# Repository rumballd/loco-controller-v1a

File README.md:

# loco-controller-v1a

NEW - Jan 2026, additional firmware examples and Handheld controller firmware

The Loco Controller is designed to offer a simple upgrade of Dapol and other locomotives to battery power and wireless control. It is highly integrated, incorporating an ESP32-C6 dual core MCU (microcontroller Unit) module together with a motor driver, voltage booster, battery charger and input power conditioner all on a single double sided PCB. 

The controller is designed as an exact replacement for the factory fitted DCC decoder adaptor installed in newer Dapol locomotives and installation consists of sliding out the factory PCB and replacing it with the controller. On the 58XX and B4 models the battery also slides in underneath the controller and is connected directly to the controller PCB.

For non Dapol locomotives there are a range of signals and power sources available on 2.54mm spacing pin headers including motor drive and LED outputs. In these cases though some disassembly of the locomotive body and soldering will be required.

Although designed primarily as a controller for motorised devices the device can also function as a generic wireless interface for signals, turnouts and other accessories. In such a ‘fixed’ application the unit can operate without a connected battery being powered solely by externally connected power sources and can drive multiple LED or servo outputs.

The controller implements a Wi-Fi access point and Web server that serves a page of locomotive specific controls to any standard web browser on a phone or tablet 

The initial hardware and firmware release supports:-

• Connector compatible with Dapol 0 Gauge 58XX and B4 locomotives

• Aux connector for other models with power, motor, LED and servo drive

• Integral voltage boost from VBAT to 12 V for the motor at 1 A

• Integral battery charger with power in via track or USB and 2mm JST socket for a 1S Li-Po battery

• Track power input is compatible with DCC and can be up to +-50 VDC with protection against inductive
 spikes
• Battery voltage and USB voltage can be monitored in firmware

• Links provided to isolate track power and the battery

• Charging is indicated by firebox LEDs in Dapol models and also in UI

• Multiple levels of over-current/over-voltage/over-temperature protection

• Integral Wi-Fi access point and Web server

• Control by standard Web browsers (up to four simultaneous connections)

• Firmware is updatable via USB connection

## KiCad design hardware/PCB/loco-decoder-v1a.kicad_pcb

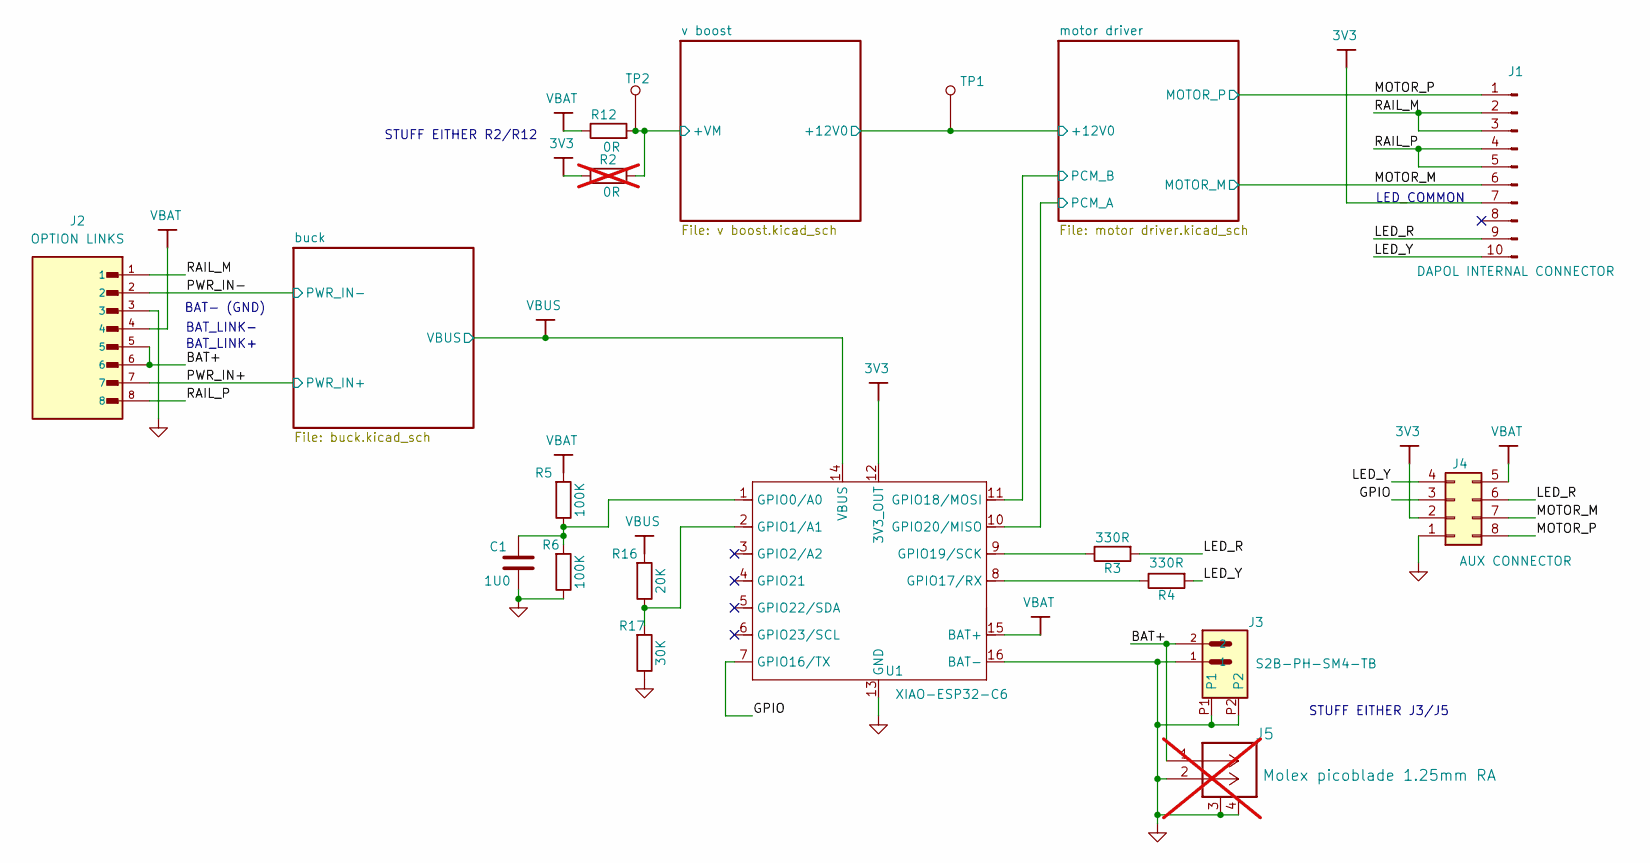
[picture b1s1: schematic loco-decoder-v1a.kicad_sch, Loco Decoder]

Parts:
C1: 1U0; C_0805_2012Metric
J1: DAPOL INTERNAL CONNECTOR; EDAC 302 SERIES CARD EDGE CONNECTOR 10way 2 row
J2: OPTION LINKS; HARWIN_M20-8890845
J3: S2B-PH-SM4-TB; JST_S2B-PH-SM4-TB
J4: AUX CONNECTOR; PinHeader_2x04_P2.54mm_Vertical
J5: Molex picoblade 1.25mm RA; CONN_532610001-SD_02_MOL; not fitted
R2: 0R; R_0805_2012Metric; not fitted
R3, R4: 330R; R_0805_2012Metric
R5, R6: 100K; R_0805_2012Metric
R12: 0R; R_0805_2012Metric
R16: 20K; R_0805_2012Metric
R17: 30K; R_0805_2012Metric
TP1, TP2: 3_Through hole test point; Test Point 1mm
U1: XIAO-ESP32-C6; XIAO-ESP32C6-SMD

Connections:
3V3: J1.7, J4.2, R2.1, U1.12 (3V3_OUT)
/BAT+: J2.5, J2.6, J3.2, J5.1
/GPIO: J4.3, U1.7 (GPIO16/TX)
/LED_R: J1.9, J4.6, R3.2
/LED_Y: J1.10, J4.4, R4.2
/MOTOR_M: J1.6, J4.7; also elsewhere on the board
/MOTOR_P: J1.1, J4.8; also elsewhere on the board
/PWR_IN+: J2.7; also elsewhere on the board
/PWR_IN-: J2.2; also elsewhere on the board
/RAIL_M: J1.2, J1.3, J2.1
/RAIL_P: J1.4, J1.5, J2.8
/motor driver/+12V0: TP1.1; also elsewhere on the board
/motor driver/PCM_A: U1.10 (GPIO20/MISO); also elsewhere on the board
/motor driver/PCM_B: U1.11 (GPIO18/MOSI); also elsewhere on the board
/v boost/+VM: R2.2, R12.2, TP2.1; also elsewhere on the board
GND: C1.2, J2.3, J3.1, J3.P1, J3.P2, J4.1, J5.2, J5.3, J5.4, R6.1, R17.1, U1.13 (GND), U1.16 (BAT-); also elsewhere on the board
unnamed: C1.1, R5.1, R6.2, U1.1 (GPIO0/A0)
unnamed: R16.1, R17.2, U1.2 (GPIO1/A1)
unnamed: R4.1, U1.8 (GPIO17/RX)
unnamed: R3.1, U1.9 (GPIO19/SCK)
VBAT: J2.4, J4.5, R5.2, R12.1, U1.15 (BAT+)
VBUS: R16.2, U1.14 (VBUS); also elsewhere on the board

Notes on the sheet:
STUFF EITHER R2/R12
STUFF EITHER J3/J5
LED_COMMON
BAT- (GND)
BAT_LINK-
BAT_LINK+

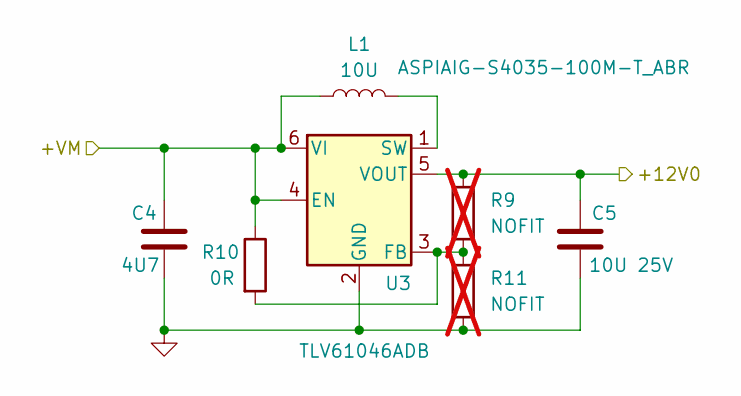
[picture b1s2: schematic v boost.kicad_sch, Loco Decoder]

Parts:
C4: 4U7; C_0805_2012Metric
C5: 10U 25V; C_1206_3216Metric
L1: 10U; IND_ASPIAIG-S4035-100M-T_ABR
R9, R11: NOFIT; R_0805_2012Metric; not fitted
R10: 0R; R_0805_2012Metric
U3: TLV61046ADB; SOT-23-6

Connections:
/motor driver/+12V0: C5.1, R9.1, U3.5 (VOUT); also elsewhere on the board
/v boost/+VM: C4.1, L1.1, R10.1, U3.4 (EN), U3.6 (VI); also elsewhere on the board
GND: C4.2, C5.2, R11.2, U3.2 (GND); also elsewhere on the board
unnamed: R9.2, R10.2, R11.1, U3.3 (FB)
unnamed: L1.2, U3.1 (SW)

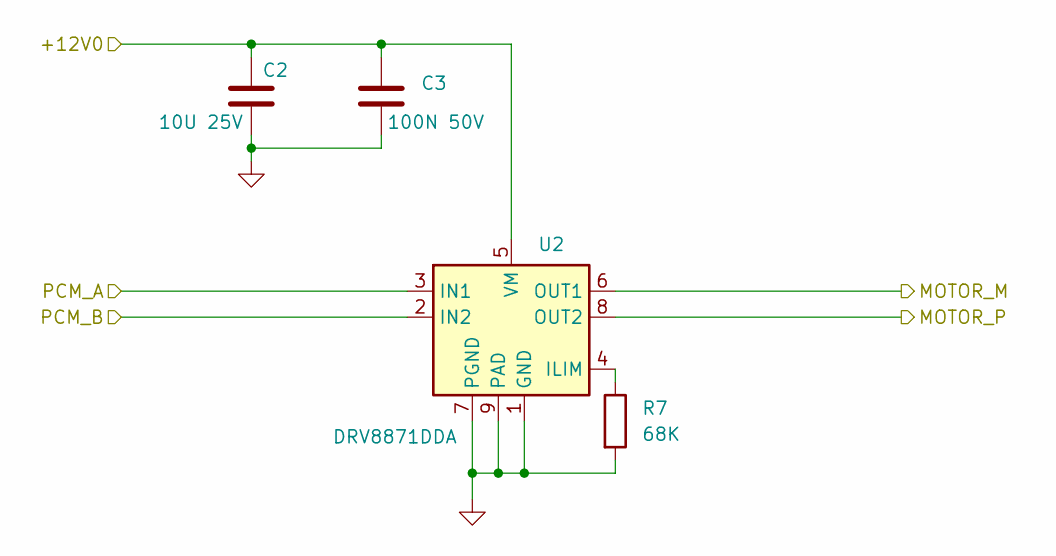
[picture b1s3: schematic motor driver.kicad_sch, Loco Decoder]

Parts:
C2: 10U 25V; C_1206_3216Metric
C3: 100N 50V; C_0805_2012Metric
R7: 68K; R_0805_2012Metric
U2: DRV8871DDA; Texas_HTSOP-8-1EP_3.9x4.9mm_P1.27mm_EP2.95x4.9mm_Mask2.4x3.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

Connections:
/MOTOR_M: U2.6 (OUT1); also elsewhere on the board
/MOTOR_P: U2.8 (OUT2); also elsewhere on the board
/motor driver/+12V0: C2.1, C3.1, U2.5 (VM); also elsewhere on the board
/motor driver/PCM_A: U2.3 (IN1); also elsewhere on the board
/motor driver/PCM_B: U2.2 (IN2); also elsewhere on the board
GND: C2.2, C3.2, R7.2, U2.1 (GND), U2.7 (PGND), U2.9 (PAD); also elsewhere on the board
unnamed: R7.1, U2.4 (ILIM)

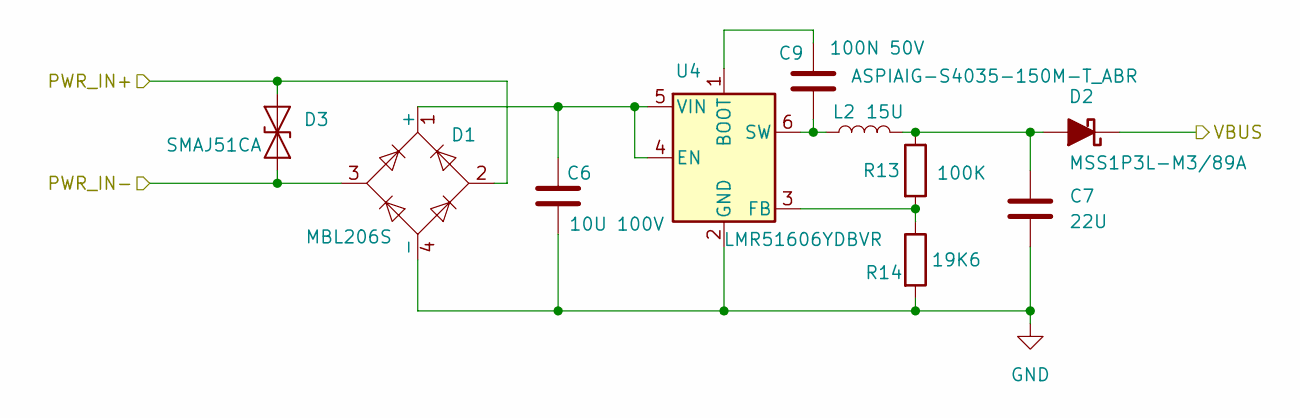
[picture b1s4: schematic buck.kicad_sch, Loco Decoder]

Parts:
C6: 10U 100V; C_1210_3225Metric
C7: 22U; C_0805_2012Metric
C9: 100N 50V; C_0805_2012Metric
D1: MBL206S; CD-MBL2xxS_BRN
D2: MSS1P3L-M3/89A; DIODE_MSP3V3-L
D3: SMAJ51CA; D_SMA
L2: 15U; WE-MAPI_4020
R13: 100K; R_0805_2012Metric
R14: 19K6; R_0805_2012Metric
U4: LMR51606YDBVR; SOT-23-6

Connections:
/PWR_IN+: D1.2, D3.1 (A1); also elsewhere on the board
/PWR_IN-: D1.3, D3.2 (A2); also elsewhere on the board
GND: C6.2, C7.2, D1.4 (-), R14.2, U4.2 (GND); also elsewhere on the board
unnamed: C6.1, D1.1 (+), U4.4 (EN), U4.5 (VIN)
unnamed: C7.1, D2.1 (A), L2.2, R13.1
unnamed: C9.1, U4.1 (BOOT)
unnamed: R13.2, R14.1, U4.3 (FB)
unnamed: C9.2, L2.1, U4.6 (SW)
VBUS: D2.2 (K); also elsewhere on the board

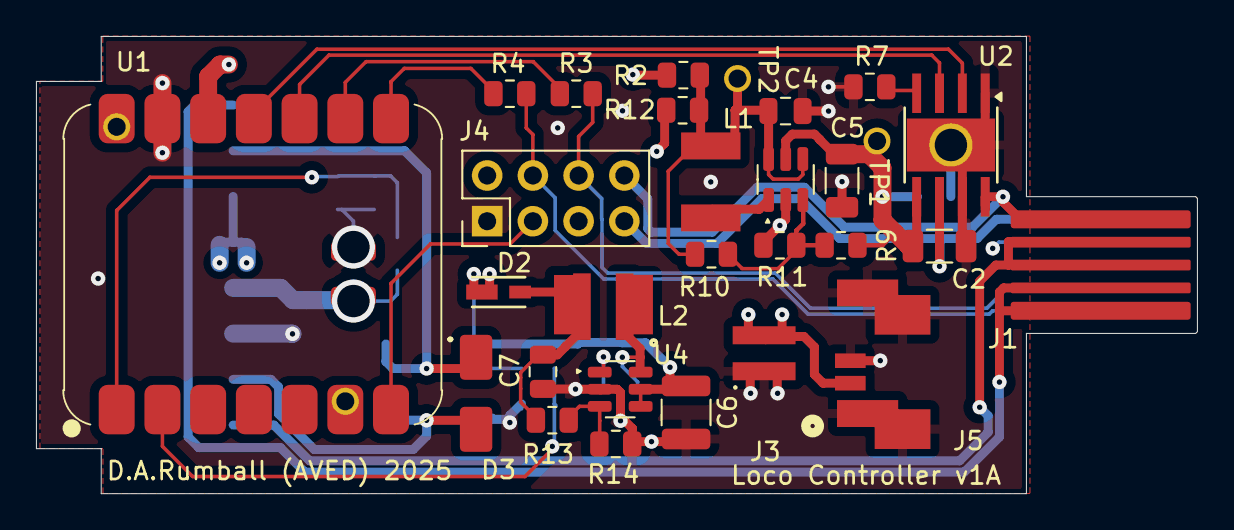
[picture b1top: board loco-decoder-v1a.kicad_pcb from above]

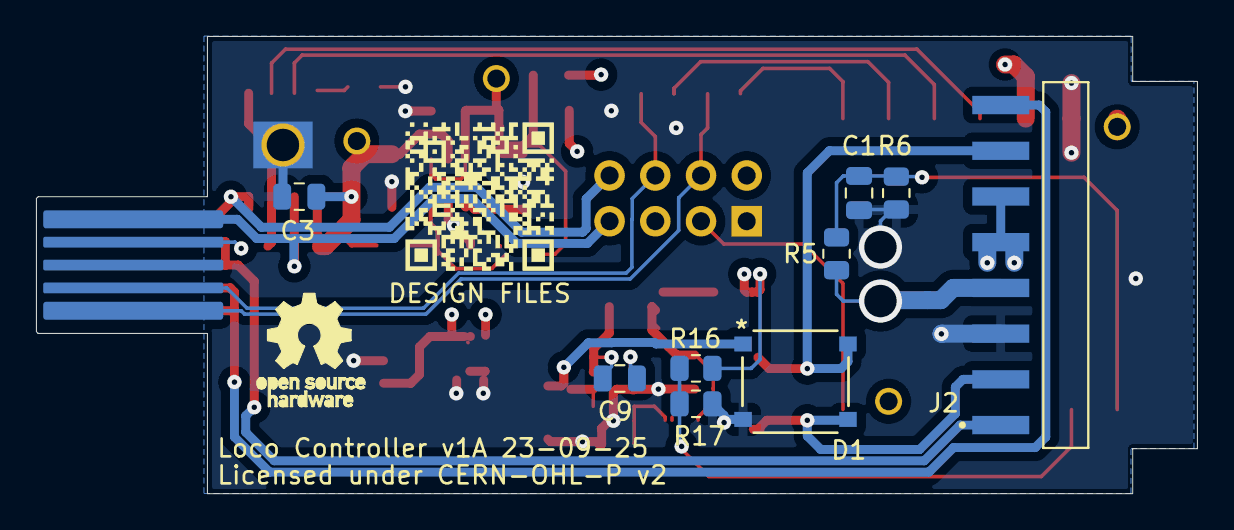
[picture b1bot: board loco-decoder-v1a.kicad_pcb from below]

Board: 4 copper layers, 64.5 x 25.4 mm, 41 parts (9 on the bottom side), 30 nets.

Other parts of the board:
DESIGN: DESIGN FILES; DESIGN FILES QR CODE
FD1, FD2: 3_Through hole test point; Test Point 1mm

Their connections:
VBUS: FD1.1; also elsewhere on the board

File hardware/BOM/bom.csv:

Designator,Footprint,Quantity,Value
C1,C_0805,1,1uF 50V X7R ±10%
"C2, C5",C_1206,2,10uF 50V X5R ±10%
"C3, C9",C_0805,2,100nF 50V X7R ±10%
C4,C_0805,1,25V 4.7uF X5R ±10%
C6,C_1210,1,100V 10uF X7S ±10%
C7,C_0805,1,10V 22uF X5R ±10%
D1,CD-MBL2xxS_BRN,1,CD-MBL206SL
D2,DIODE_MSP3V3-L,1,MSS1P3L-M3/89A
D3,D_SMA,1,SMAJ51CA
J2,1X8_P2.54MM_RA,1,HARWIN_M20-8890845
J3,JST_S2B-PH-SM4-TB,1,S2B-PH-SM4-TB
J4,2X4_P2.54MM_VERT,1,AUX CONNECTOR
L1,"SMD,4x4mm",1,10U IND_ASPIAIG-S4035-100M-T_ABR
L2,"SMD,4x4mm",1,15U IND_ASPIAIG-S4035-150M-T_ABR
"R10, R12",R_0805,2,0R 125mW ±1%
"R13, R5, R6",R_0805,3,100K 125mW ±1%
R14,R_0805,1,19K6 125mW ±1%
R16,R_0805,1,20K 125mW ±1%
R17,R_0805,1,30K 125mW ±1%
"R3, R4",R_0805,2,330R 125mW ±1%
R7,R_0805,1,68K 125mW ±1%
U1,XIAO-ESP32C6-SMD,1,XIAO-ESP32-C6
U2,HTSOP-8,1,DRV8871DDAR
U3,SOT-23-6,1,TLV61046ADB
U4,SOT-23-6,1,LMR51606YDBVR

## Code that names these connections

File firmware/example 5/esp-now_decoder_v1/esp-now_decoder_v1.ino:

//
// Simple POC for control of locomotive usung the ESP-NOW protocol
// based on target example by VolosR 
// github.com/VolosR/Knob18Meters/tree/main/KnobRGBControl
// 

// v1 - initial version

#include <Arduino.h>
#include <WiFi.h>
#include <esp_now.h>

// hardware defines
// LEDs
#define USER_LED          15   // GPIO pin for heartbeat LED
#define LED_TIMEOUT       250  //Heartbeat LED cycle time in ms
#define FLICKER_TIMEOUT   66  //Firebox LED cycle time in ms
// H-bridge control outputs
#define IN1        18
#define IN2        20
// Firebox LED outputs
#define LED_R      17
#define LED_Y      19
// VBUS input (digital)
#define VBUS        1
// VBAT input (analogue)
#define VBAT        0
// expansion connector GPIO
#define EXT_GPIO   16

#include <loco_profiles.h> // build configs and specific loco profiles for motor control etc

#define DEBUG        0 // 0 = no debug

int8_t rxPower[4] = {0,0,0,0};   // (power for the selected loco in the UI), loco1, loco2, loco3
int8_t txStatus[4] = {0,0,0,0};   // LOCO_ID, spare, spare, vbat as % plus charging state

// motor
int power = 0;
int motor_power = 0;
int old_speed = 0;
float nudge = 0.0;

//LEDs
int lastFlickerTime = 0;
int lastLedTime = 0;
int ledState = 0;

int vbat = 0;

// handheld control MAC address
extern uint8_t targetAdress[] = {0xD0, 0xCF, 0x13, 0x1E, 0x12, 0x50}; // control unit address

esp_now_peer_info_t peerInfo;

// callback when data is sent
void OnDataSent(const uint8_t *mac_addr, esp_now_send_status_t status) {
  Serial.print("\r\nLast Packet Send Status:\t");
  Serial.println(status == ESP_NOW_SEND_SUCCESS ? "Delivery Success" : "Delivery Fail");
}


// callback for ESP-NOW packet Rx
void OnDataRecv(const uint8_t * mac, const uint8_t *incomingData, int len) {
  memcpy(&rxPower, incomingData, sizeof(rxPower)); // copy the 4 bytes we use
}

void setup() {
  Serial.begin(115200);
  Serial.println("startup");

   WiFi.mode(WIFI_STA);

  // Init ESP-NOW
  if (esp_now_init() != ESP_OK) {
    Serial.println("Error initializing ESP-NOW");
    return;
  }
  esp_now_register_recv_cb(esp_now_recv_cb_t(OnDataRecv));

  esp_now_register_send_cb(esp_now_send_cb_t(OnDataSent)); // cast to fix ESP_NOW API change 
  memcpy(peerInfo.peer_addr, targetAdress, 6);
  peerInfo.channel = 0;  
  peerInfo.encrypt = false;

  // Add peer        
  if (esp_now_add_peer(&peerInfo) != ESP_OK){
    Serial.println("Failed to add peer");
    return;
  }
  
 // Set motor connections as outputs
  pinMode(IN1, OUTPUT);
  pinMode(IN2, OUTPUT);

// set up PWM
  ledcAttach(IN1, PWM_FREQ, PWM_BITS);
  ledcAttach(IN2, PWM_FREQ, PWM_BITS);
 
// Stop motor (Hi-Z)
  digitalWrite(IN1, LOW);
  digitalWrite(IN2, LOW);

// set up on board 'heartbeat' LED
  pinMode(USER_LED, OUTPUT);
  ledcAttach(USER_LED, PWM_FREQ, PWM_BITS);  

#ifdef FIREBOX_LEDS
// set up firebox LEDs
  pinMode(LED_Y,    OUTPUT);
  pinMode(LED_R,    OUTPUT);
  ledcAttach(LED_Y,    PWM_FREQ, PWM_BITS);  
  ledcAttach(LED_R,    PWM_FREQ, PWM_BITS);

// firebox LEDs are initially off (1 = off)
  ledcWrite(LED_Y, 255);
  ledcWrite(LED_R, 255);
#endif

// 'charge' detection is by sensing VBUS 
  pinMode(VBUS, INPUT);

}

void loop() {

// it's alive! LED
  if ((millis() - lastLedTime) > LED_TIMEOUT) {
 
    lastLedTime = millis();

    if (ledState == 0) {

      ledcWrite(USER_LED, 255);
      ledState++;

    } else { 

      ledcWrite(USER_LED, 0);
      ledState--;

  // read battery voltage (average over 16 readings)
      vbat = 0;
      for (int i=0; i<16; i++) {
        vbat += (analogReadMilliVolts(VBAT) * 2); // VBAT input is via a 2:1 resistive divider
      }
      vbat /= 16;

// build status packet      
      txStatus[3] = map(vbat, 3000, 4200, 0, 100); //3.00V->4.2V maps to 0->100%
      if (digitalRead(VBUS)) {
        txStatus[3] |= 0x80; // set msb if charging
      }
      txStatus[0] = LOCO_ID;

// send the status packet
esp_err_t result = esp_now_send(targetAdress, (uint8_t *) &txStatus, sizeof(txStatus));

    }
  }

#ifdef FIREBOX_LEDS
  if ((millis() - lastFlickerTime) > FLICKER_TIMEOUT) {
 
    lastFlickerTime = millis();

// FIXME - this needs to be tied to actual charging rather than bus power present
    if (digitalRead(VBUS)) {             // only illuminate firebox if charging
      ledcWrite(LED_R, 255-(random(180)+75));
      ledcWrite(LED_Y, 255-(random(90)+65));
    } else {                            //LEDs off
      ledcWrite(LED_Y, 255);
      ledcWrite(LED_R, 255);
    }
  } 
# endif

// calculate motor power and set PWM channel according to direction
  power = (int)abs(rxPower[LOCO_ID]); // note cast from CHAR to INT

  if (abs(rxPower[LOCO_ID]) == rxPower[LOCO_ID]) { // -ve values are reverse
  
    motor_power = map(power, 0, 100, FWD_DEAD_BAND, MAX_POWER);
  
    if ((old_speed == 0) && power != 0) {  // 'nudge' motor on start
      nudge = INITIAL_NUDGE;
    }
    motor_power += int(nudge);
    motor_power = (motor_power < 0) ? 0 : motor_power; //clamp motor_power
    motor_power = (motor_power > MAX_POWER) ? MAX_POWER : motor_power;
    
    nudge -= NUDGE_DECAY;
    nudge = (nudge < 0.0) ? 0.0 : nudge;

    motor_power = (motor_power <= FWD_DEAD_BAND) ? 0 : motor_power; // force a stop at DEAD_BAND value

    ledcWrite(IN1, 0);
    ledcWrite(IN2, motor_power);

  } else {
  
    motor_power = map(power, 0, 100, REV_DEAD_BAND, MAX_POWER);
  
    if ((old_speed == 0) && power != 0) {  // 'nudge' motor on start
      nudge = INITIAL_NUDGE;
    }
        motor_power += int(nudge);
    motor_power = (motor_power < 0) ? 0 : motor_power; //clamp motor_power
    motor_power = (motor_power > MAX_POWER) ? MAX_POWER : motor_power;
    
    nudge -= NUDGE_DECAY;
    nudge = (nudge < 0.0) ? 0.0 : nudge;

    motor_power = (motor_power <= REV_DEAD_BAND) ? 0 : motor_power; // force a stop at DEAD_BAND value

    ledcWrite(IN2, 0);
    ledcWrite(IN1, motor_power);

  }
  
  old_speed = power;

  if (DEBUG) {
  Serial.print("power = ");
  Serial.print(power, DEC);
  Serial.print("   motor_power = ");
  Serial.print(motor_power, DEC);
  Serial.print("   nudge = ");
  Serial.print(nudge, DEC);
  Serial.print("   old_speed = ");
  Serial.println(old_speed, DEC);
  }

//delay(1);

}

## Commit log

2025-11-08 documentation tweak
2025-11-11 Add pdf schematic
2026-01-12 add handheld control and 08/09 controller firmware
2026-01-12 fix handheld control image

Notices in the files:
hardware/PCB/loco-decoder-v1a.kicad_pcb:
Licensed under CERN-OHL-P v2
